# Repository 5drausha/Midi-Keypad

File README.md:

# Midi-Keypad

This week, I decided to make the starter project, the MIDI keypad. 

This is my final render of the project. 
This project is slightly tweaked compared to the starter guide. It has 10 piano keys, a rotary encoder. 2 MX switches, a passive buzzer, and an ESP32-S3-Zero. I changed it a little bit because of the pricing of the parts in the tutorial and also to make something that is more practically useful. The rotary encoder will be used for volume control, the buzzer can be used for playing the music from the piano, and the switches can be used to switch modes or key tones.
I haven't made any firmware for this project yet, so I am just going to use the firmware used in the tutorial. 
Below are my PCB and Schematic:

The total parts cost of this project is $21.65. I have excluded a buzzer from my BOM since I already have one. Below are screenshots of my carts and the BOM:

This was a fun project, and I learnt a lot from it, mainly about PCB and capacitative touch. Although I'm not much of a music guy, I enjoyed this project, and thanks again for this opportunity Half Life!

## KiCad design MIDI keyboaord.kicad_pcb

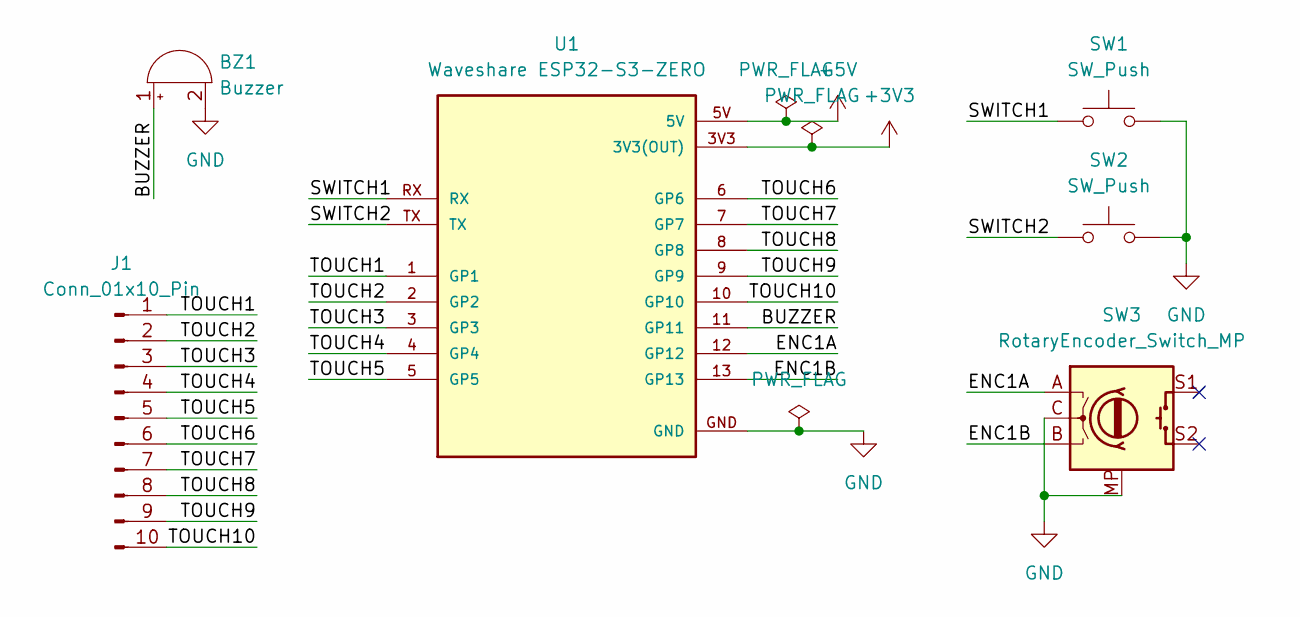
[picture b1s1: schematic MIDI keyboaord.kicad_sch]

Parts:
BZ1: Buzzer; Buzzer_12x9.5RM7.6
J1: Conn_01x10_Pin; keyboard revised
SW1, SW2: SW_Push; SW_Cherry_MX_1.00u_PCB
SW3: RotaryEncoder_Switch_MP; RotaryEncoder_Alps_EC11E-Switch_Vertical_H20mm
U1: Waveshare ESP32-S3-ZERO; Waveshare ESP32-S3-Zero; PARTREV NA

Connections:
+3V3: U1.3V3 (3V3(OUT))
+5V: U1.5V
/BUZZER: BZ1.1 (+), U1.11 (GP11)
/ENC1A: SW3.A, U1.12 (GP12)
/ENC1B: SW3.B, U1.13 (GP13)
/SWITCH1: SW1.1, U1.RX
/SWITCH2: SW2.1, U1.TX
/TOUCH1: J1.1, U1.1 (GP1)
/TOUCH2: J1.2, U1.2 (GP2)
/TOUCH3: J1.3, U1.3 (GP3)
/TOUCH4: J1.4, U1.4 (GP4)
/TOUCH5: J1.5, U1.5 (GP5)
/TOUCH6: J1.6, U1.6 (GP6)
/TOUCH7: J1.7, U1.7 (GP7)
/TOUCH8: J1.8, U1.8 (GP8)
/TOUCH9: J1.9, U1.9 (GP9)
/TOUCH10: J1.10, U1.10 (GP10)
GND: BZ1.2 (-), SW1.2, SW2.2, SW3.C, SW3.MP, U1.GND

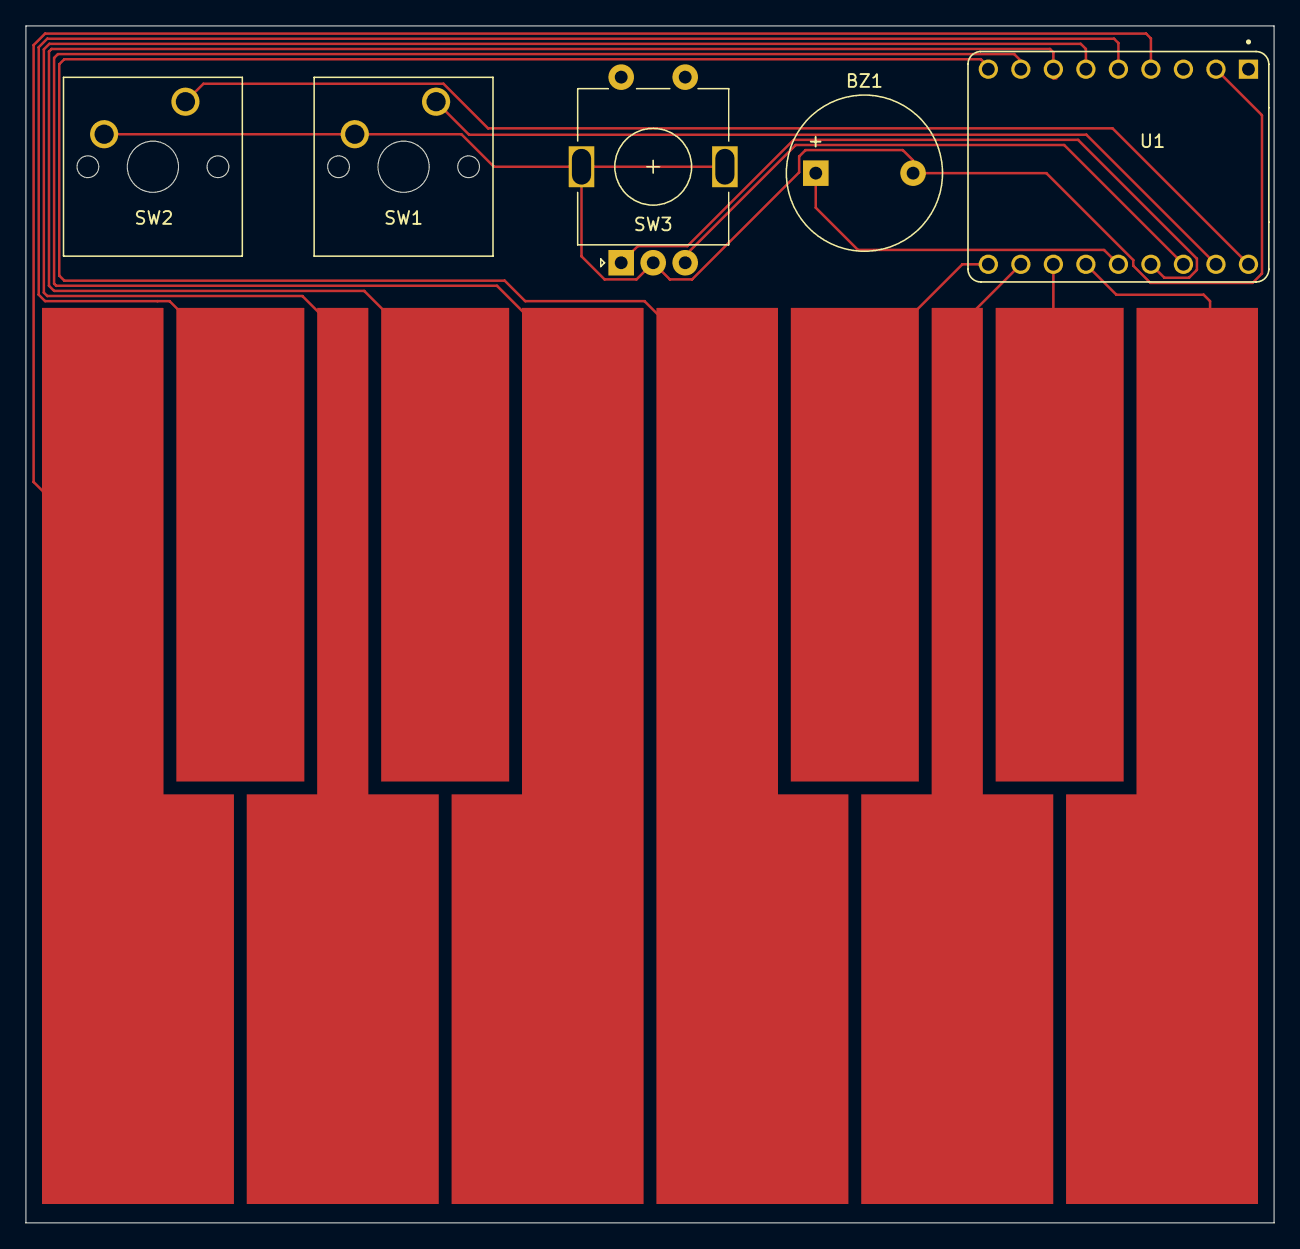
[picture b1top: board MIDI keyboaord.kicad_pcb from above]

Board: 2 copper layers, 97.5 x 93.5 mm, 6 parts (0 on the bottom side), 16 nets.
